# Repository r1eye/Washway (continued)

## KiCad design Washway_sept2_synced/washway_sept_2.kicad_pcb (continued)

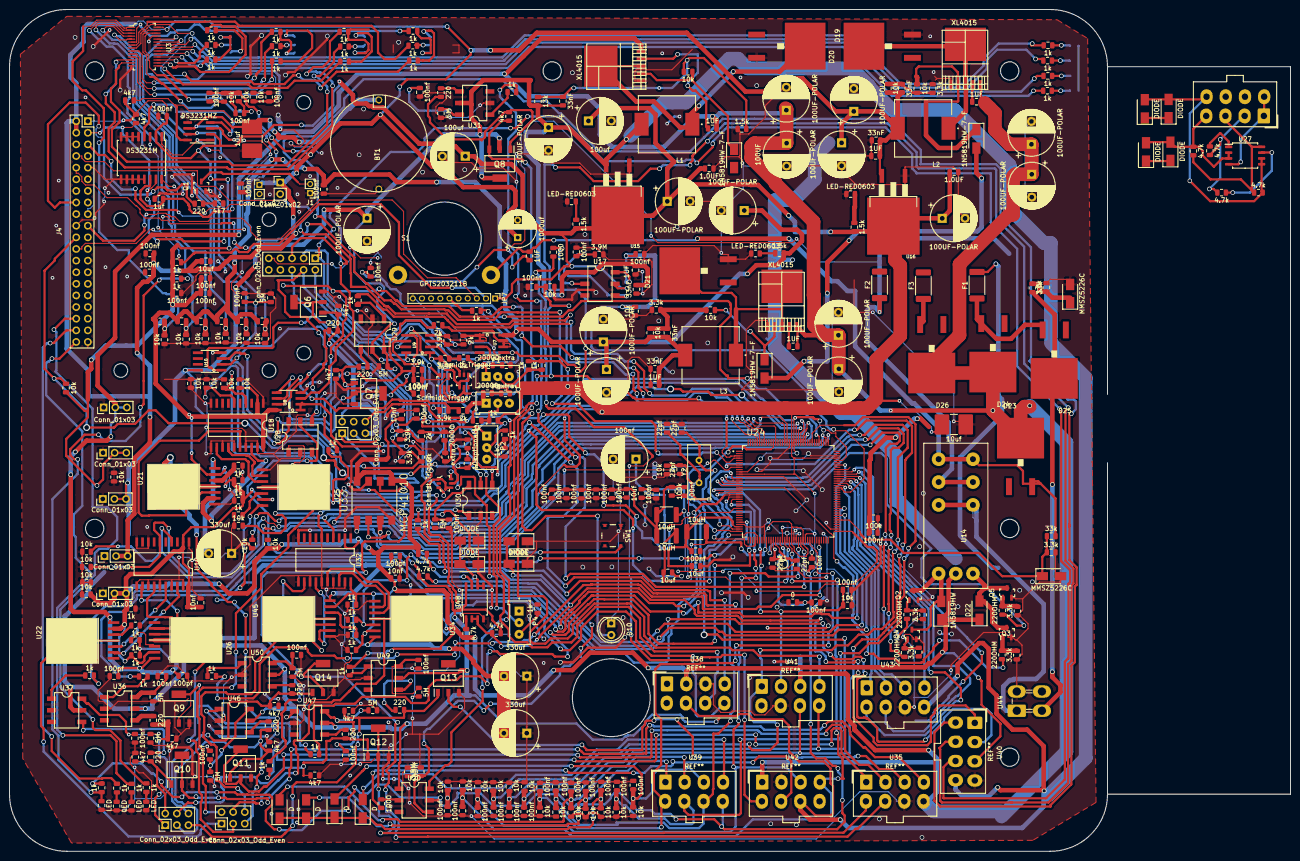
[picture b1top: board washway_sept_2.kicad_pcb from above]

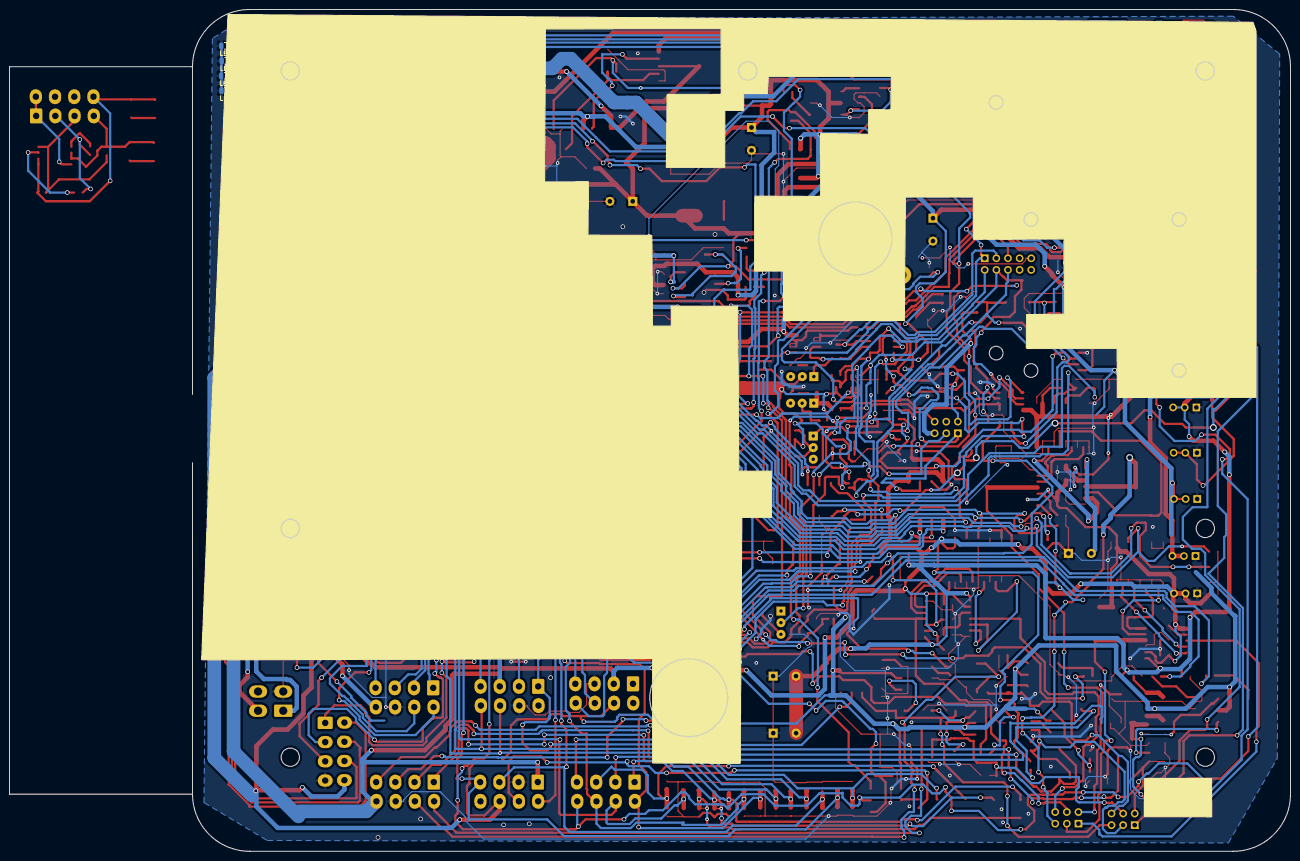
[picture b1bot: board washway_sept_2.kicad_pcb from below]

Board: 2 copper layers, 280.0 x 184.0 mm, 435 parts (8 on the bottom side), 283 nets.

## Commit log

2020-09-02 just pushing
